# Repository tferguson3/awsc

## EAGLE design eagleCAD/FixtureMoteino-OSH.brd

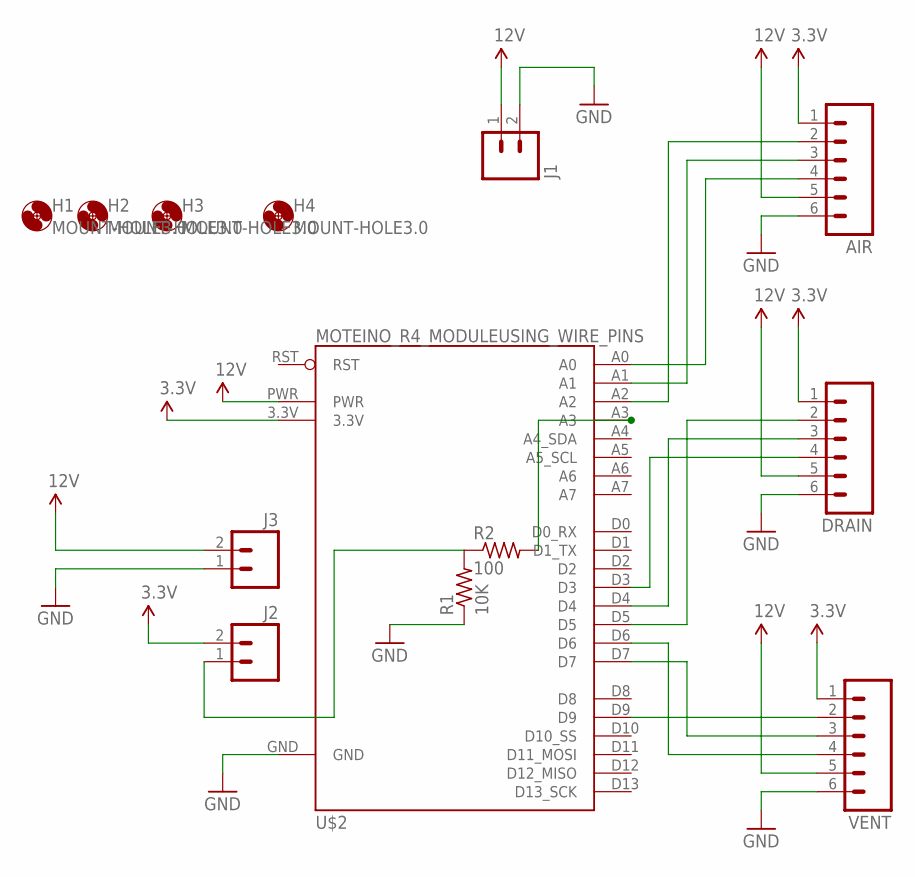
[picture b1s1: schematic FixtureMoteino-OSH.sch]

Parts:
AIR: M06LOCK_LONGPADS; 1X06_LOCK_LONGPADS
DRAIN: M06LOCK_LONGPADS; 1X06_LOCK_LONGPADS
H1, H2, H3, H4: MOUNT-HOLE3.0; 3,0
J1, J2, J3: M025MM; SCREWTERMINAL-5MM-2
R1: 10K; 0207/10
R2: 100; 0207/10
U$2: MOTEINO_R4_MODULEUSING_WIRE_PINS; MOTEINO_R4_WIRE
VENT: M06LOCK_LONGPADS; 1X06_LOCK_LONGPADS

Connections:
3.3V: AIR.1, DRAIN.1, J2.2, U$2.3.3V, VENT.1
12V: AIR.5, DRAIN.5, J1.1, J3.2, U$2.PWR, VENT.5
GND: AIR.6, DRAIN.6, J1.2, J3.1, R1.1, U$2.GND, VENT.6
unnamed: DRAIN.4, U$2.D3
unnamed: DRAIN.3, U$2.D4
unnamed: DRAIN.2, U$2.D5
unnamed: U$2.D6, VENT.4
unnamed: J2.1, R1.2, R2.1
unnamed: U$2.D7, VENT.3
unnamed: U$2.D9, VENT.2
unnamed: AIR.4, U$2.A0
unnamed: AIR.3, U$2.A1
unnamed: AIR.2, U$2.A2
unnamed: R2.2, U$2.A3

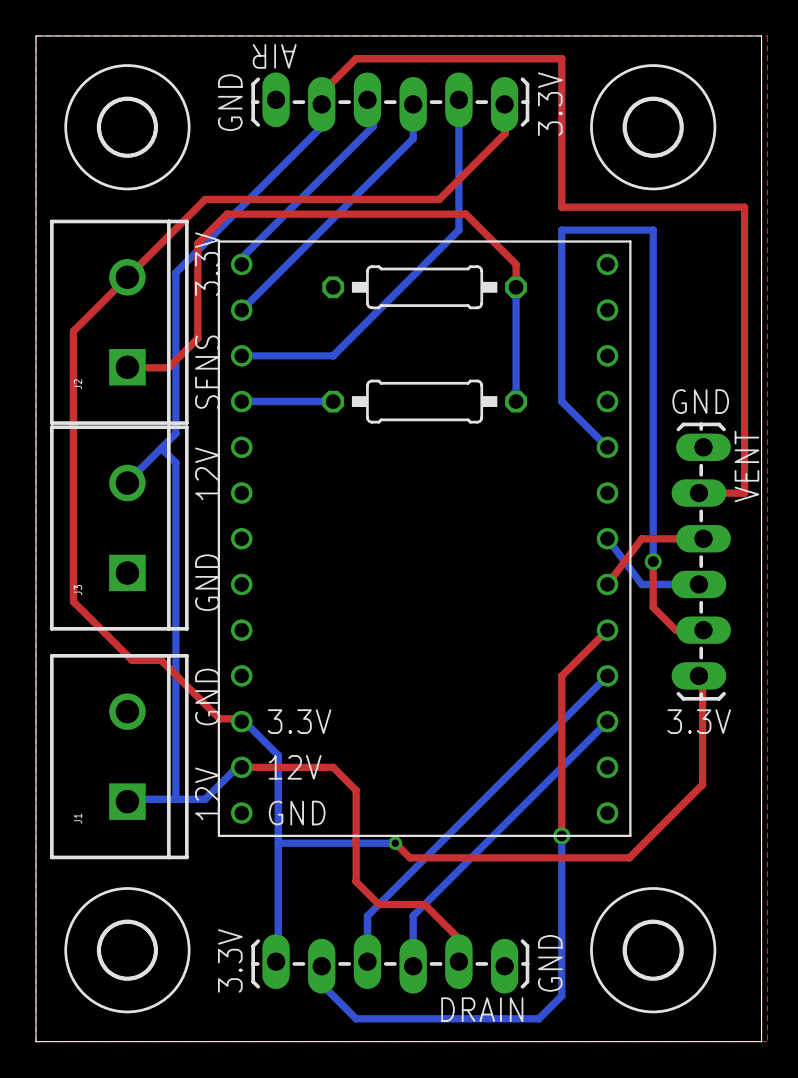
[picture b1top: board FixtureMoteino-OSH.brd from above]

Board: 2 copper layers, 40.3 x 55.9 mm, 14 parts (1 on the bottom side), 14 nets.

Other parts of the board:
U$1: OSHW-LOGO-L

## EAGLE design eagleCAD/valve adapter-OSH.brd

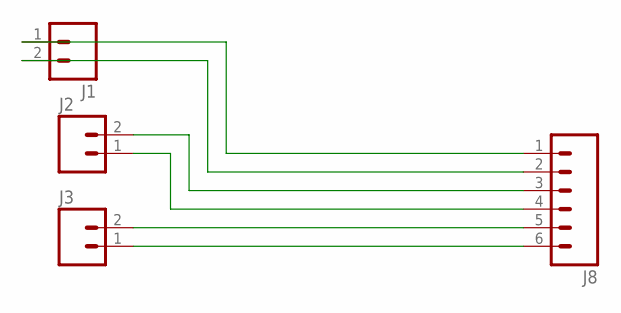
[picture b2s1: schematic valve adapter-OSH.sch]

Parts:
J1, J2, J3: M025MM; SCREWTERMINAL-5MM-2
J8: M06LOCK_LONGPADS; 1X06_LOCK_LONGPADS

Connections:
unnamed: J1.1, J8.1
unnamed: J1.2, J8.2
unnamed: J2.2, J8.3
unnamed: J2.1, J8.4
unnamed: J3.2, J8.5
unnamed: J3.1, J8.6

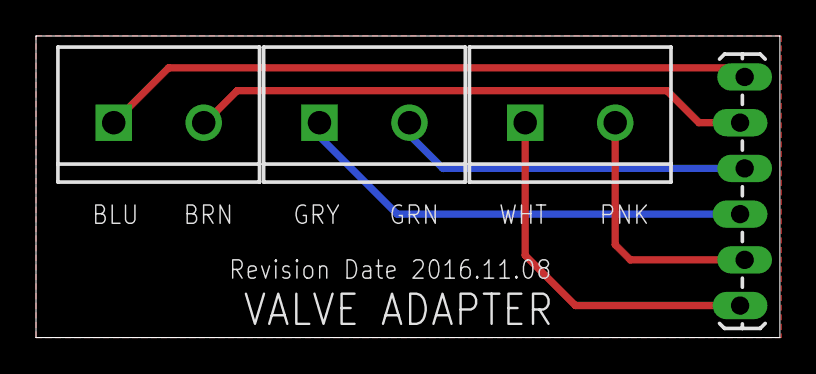
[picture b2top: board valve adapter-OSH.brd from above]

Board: 2 copper layers, 41.3 x 16.8 mm, 5 parts (1 on the bottom side), 6 nets.

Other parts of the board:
U$1: OSHW-LOGO-L

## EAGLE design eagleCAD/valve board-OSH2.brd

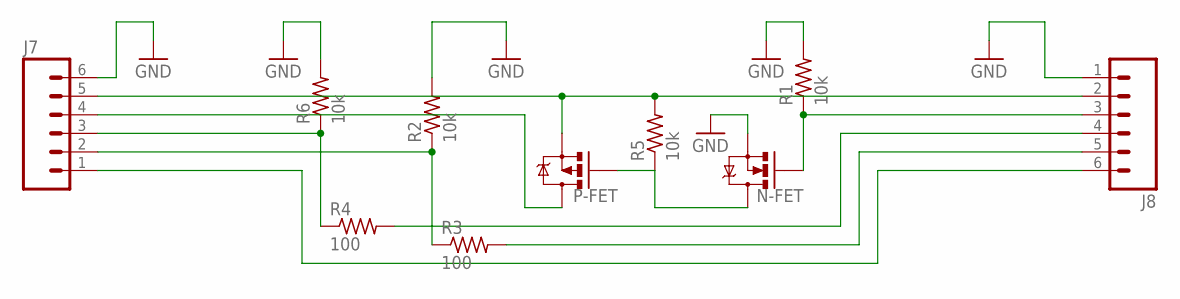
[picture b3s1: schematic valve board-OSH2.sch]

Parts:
J7, J8: M06LOCK_LONGPADS; 1X06_LOCK_LONGPADS
N-FET: MOSFET-NCHANNELFQP30N06L; TO220V
P-FET: MOSFET-PCHANNELFQP27P06; TO220V
R1, R2, R5, R6: 10k; 0207/10
R3, R4: 100; 0207/10

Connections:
GND: J7.6, J8.1, N-FET.3 (S), R1.2, R2.2, R6.2
unnamed: J8.4, R4.2
unnamed: J8.5, R3.2
unnamed: J7.4, P-FET.2 (D)
unnamed: J7.5, J8.2, P-FET.3 (S), R5.2
unnamed: J7.2, R2.1, R3.1
unnamed: N-FET.2 (D), P-FET.1 (G), R5.1
unnamed: J8.3, N-FET.1 (G), R1.1
unnamed: J7.3, R4.1, R6.1
unnamed: J7.1, J8.6

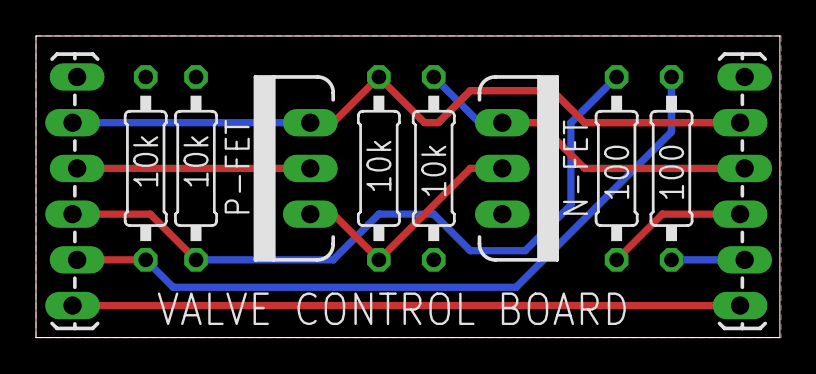
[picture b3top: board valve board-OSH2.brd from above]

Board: 2 copper layers, 41.3 x 16.8 mm, 11 parts (1 on the bottom side), 10 nets.

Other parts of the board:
U$1: OSHW-LOGO-L

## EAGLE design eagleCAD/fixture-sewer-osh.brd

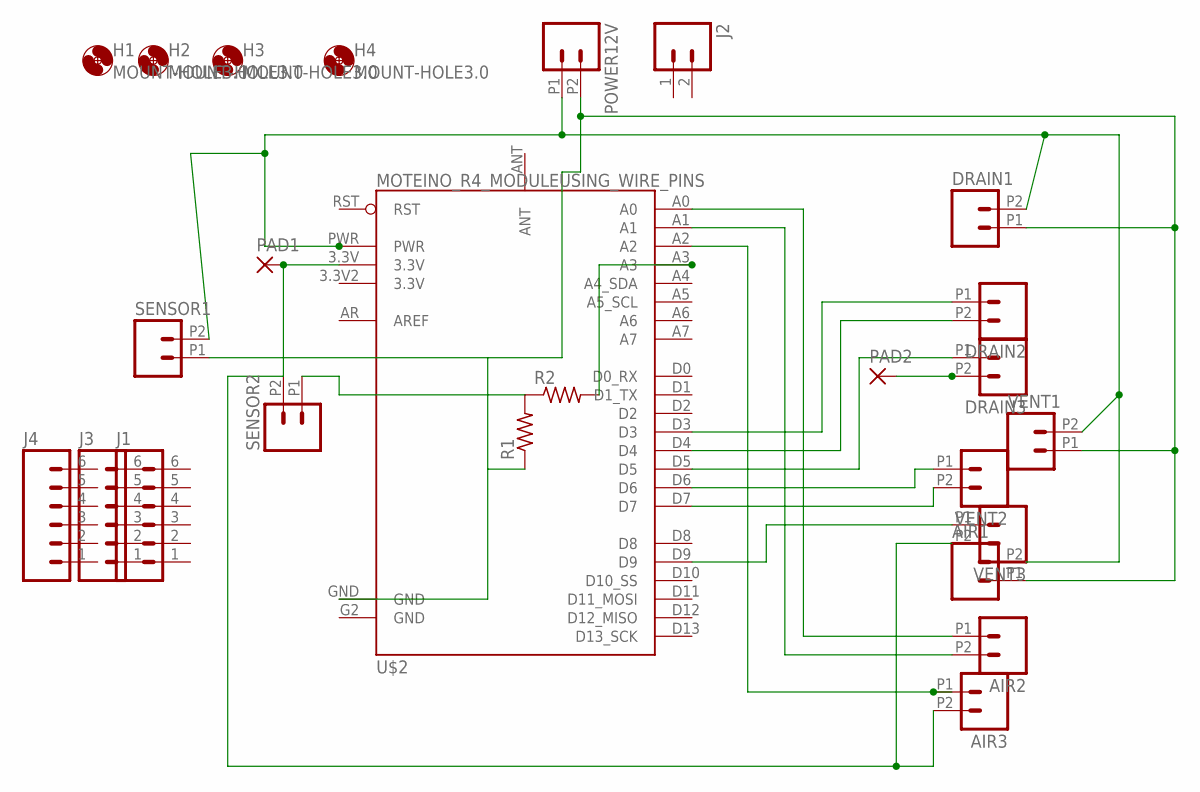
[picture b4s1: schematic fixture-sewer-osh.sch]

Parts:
AIR1, AIR2, AIR3: M022.54MM_SCREWTERM; 1X02_2.54_SCREWTERM
DRAIN1, DRAIN2, DRAIN3: M022.54MM_SCREWTERM; 1X02_2.54_SCREWTERM
H1, H2, H3, H4: MOUNT-HOLE3.0; 3,0
J1, J3, J4: M06LOCK_LONGPADS; 1X06_LOCK_LONGPADS
J2: M025MM; SCREWTERMINAL-5MM-2
PAD1, PAD2: 2,15/1,0
POWER12V: M022.54MM_SCREWTERM; 1X02_2.54_SCREWTERM
R1, R2: R-US_0207/10; 0207/10
SENSOR1, SENSOR2: M022.54MM_SCREWTERM; 1X02_2.54_SCREWTERM
U$2: MOTEINO_R4_MODULEUSING_WIRE_PINS; MOTEINO_R4_WIRE
VENT1, VENT2, VENT3: M022.54MM_SCREWTERM; 1X02_2.54_SCREWTERM

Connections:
GND: AIR1.P1 (1), DRAIN1.P1 (1), POWER12V.P2 (2), R1.1, SENSOR1.P1 (1), U$2.G2 (GND), U$2.GND, VENT1.P1 (1)
unnamed: AIR1.P2 (2), DRAIN1.P2 (2), POWER12V.P1 (1), SENSOR1.P2 (2), U$2.PWR, VENT1.P2 (2)
unnamed: DRAIN2.P1 (1), U$2.D3
unnamed: DRAIN2.P2 (2), U$2.D4
unnamed: DRAIN3.P1 (1), U$2.D5
unnamed: U$2.D6, VENT2.P1 (1)
unnamed: R1.2, R2.1, SENSOR2.P1 (1)
unnamed: U$2.D7, VENT2.P2 (2)
unnamed: U$2.D9, VENT3.P1 (1)
unnamed: AIR2.P1 (1), U$2.A0
unnamed: AIR2.P2 (2), U$2.A1
unnamed: AIR3.P1 (1), U$2.A2
unnamed: DRAIN3.P2 (2), PAD2.1
unnamed: AIR3.P2 (2), PAD1.1, SENSOR2.P2 (2), U$2.3.3V, VENT3.P2 (2)
unnamed: R2.2, U$2.A3

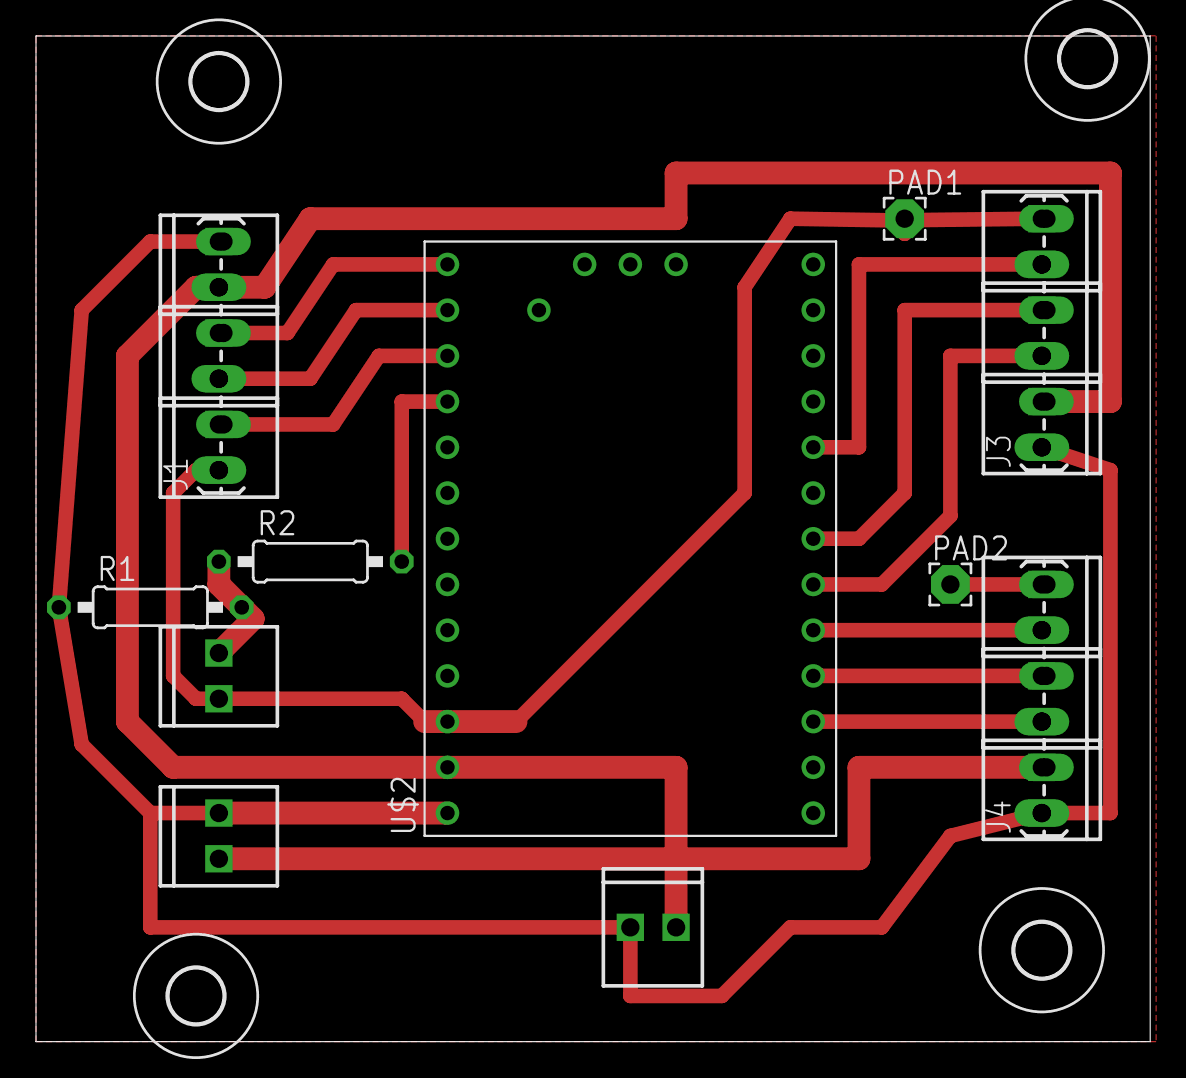
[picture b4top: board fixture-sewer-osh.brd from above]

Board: 2 copper layers, 61.9 x 55.9 mm, 24 parts (0 on the bottom side), 15 nets.

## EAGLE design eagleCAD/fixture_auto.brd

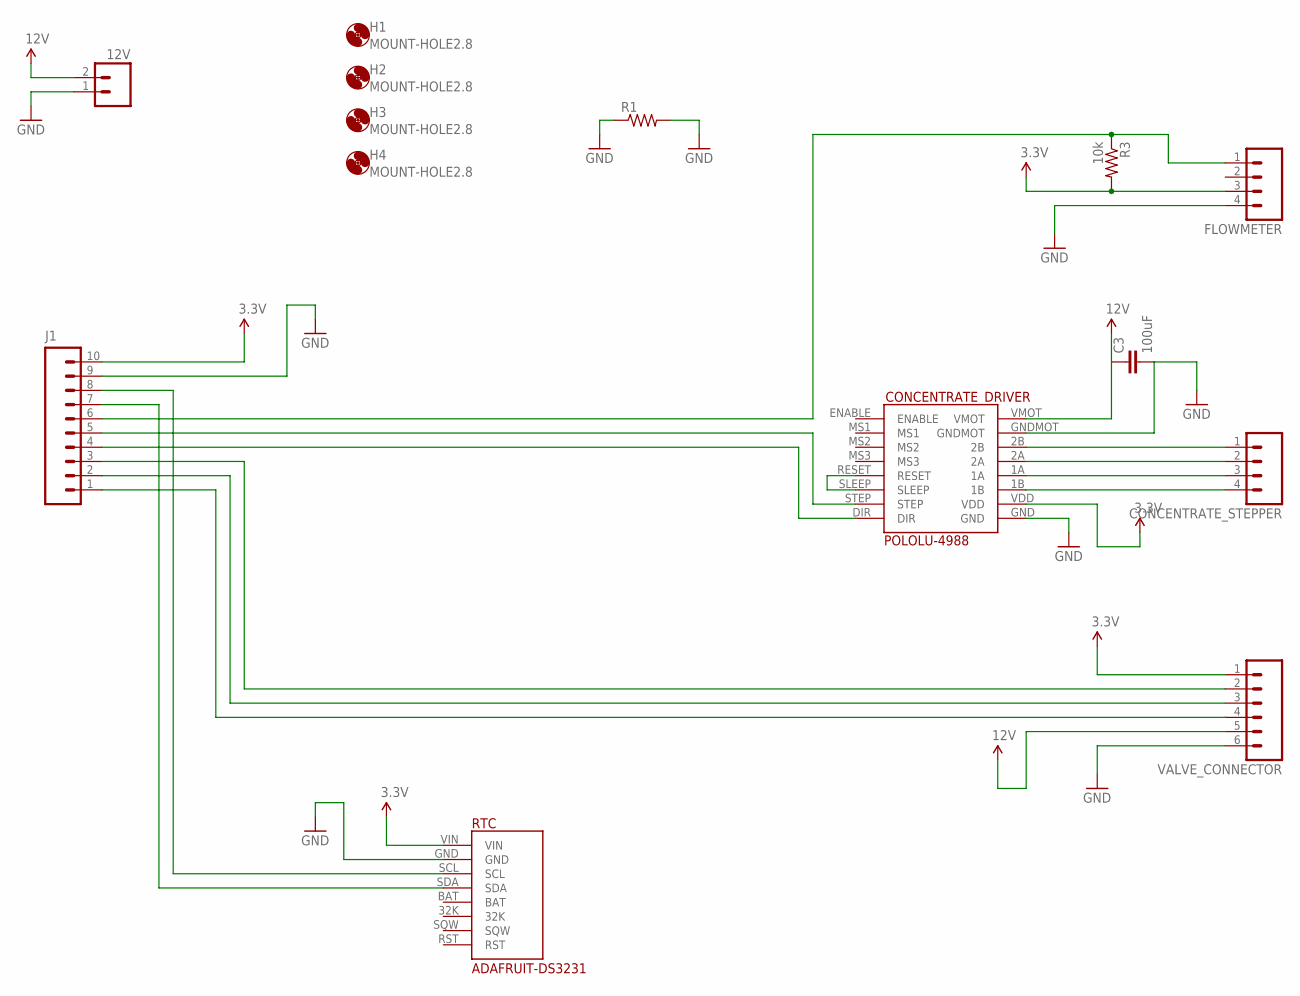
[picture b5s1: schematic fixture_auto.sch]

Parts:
12V: M02LOCK_LONGPADS; 1X02_LOCK_LONGPADS
C3: 100uF; CAP-PTH-SMALL-KIT
CONCENTRATE_DRIVER: POLOLU-4988
CONCENTRATE_STEPPER: M04LOCK_LONGPADS; 1X04_LOCK_LONGPADS
FLOWMETER: M04LOCK_LONGPADS; 1X04_LOCK_LONGPADS
H1, H2, H3, H4: MOUNT-HOLE2.8; 2,8
J1: M10LOCK_LONGPADS; 1X10_LOCK_LONGPADS
R1: RESISTORPTH-1/2W; AXIAL-0.5
R3: 10k; AXIAL-0.3EZ
RTC: ADAFRUIT-DS3231
VALVE_CONNECTOR: M06LOCK_LONGPADS; 1X06_LOCK_LONGPADS

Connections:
3.3V: CONCENTRATE_DRIVER.VDD, FLOWMETER.3, J1.10, R3.P$2 (2), RTC.VIN, VALVE_CONNECTOR.1
12V: 12V.2, C3.1, CONCENTRATE_DRIVER.VMOT, VALVE_CONNECTOR.5
FLOW_PULSE: FLOWMETER.1, J1.6, R3.P$1 (1)
GND: 12V.1, C3.2, CONCENTRATE_DRIVER.GND, CONCENTRATE_DRIVER.GNDMOT, FLOWMETER.4, J1.9, R1.P$1 (1), R1.P$2 (2), RTC.GND, VALVE_CONNECTOR.6
unnamed: J1.3, VALVE_CONNECTOR.2
unnamed: J1.2, VALVE_CONNECTOR.3
unnamed: CONCENTRATE_DRIVER.2B, CONCENTRATE_STEPPER.1
unnamed: J1.1, VALVE_CONNECTOR.4
unnamed: CONCENTRATE_DRIVER.2A, CONCENTRATE_STEPPER.2
unnamed: CONCENTRATE_DRIVER.1A, CONCENTRATE_STEPPER.3
unnamed: CONCENTRATE_DRIVER.1B, CONCENTRATE_STEPPER.4
unnamed: CONCENTRATE_DRIVER.RESET, CONCENTRATE_DRIVER.SLEEP
unnamed: CONCENTRATE_DRIVER.STEP, J1.5
unnamed: CONCENTRATE_DRIVER.DIR, J1.4
unnamed: J1.8, RTC.SCL
unnamed: J1.7, RTC.SDA

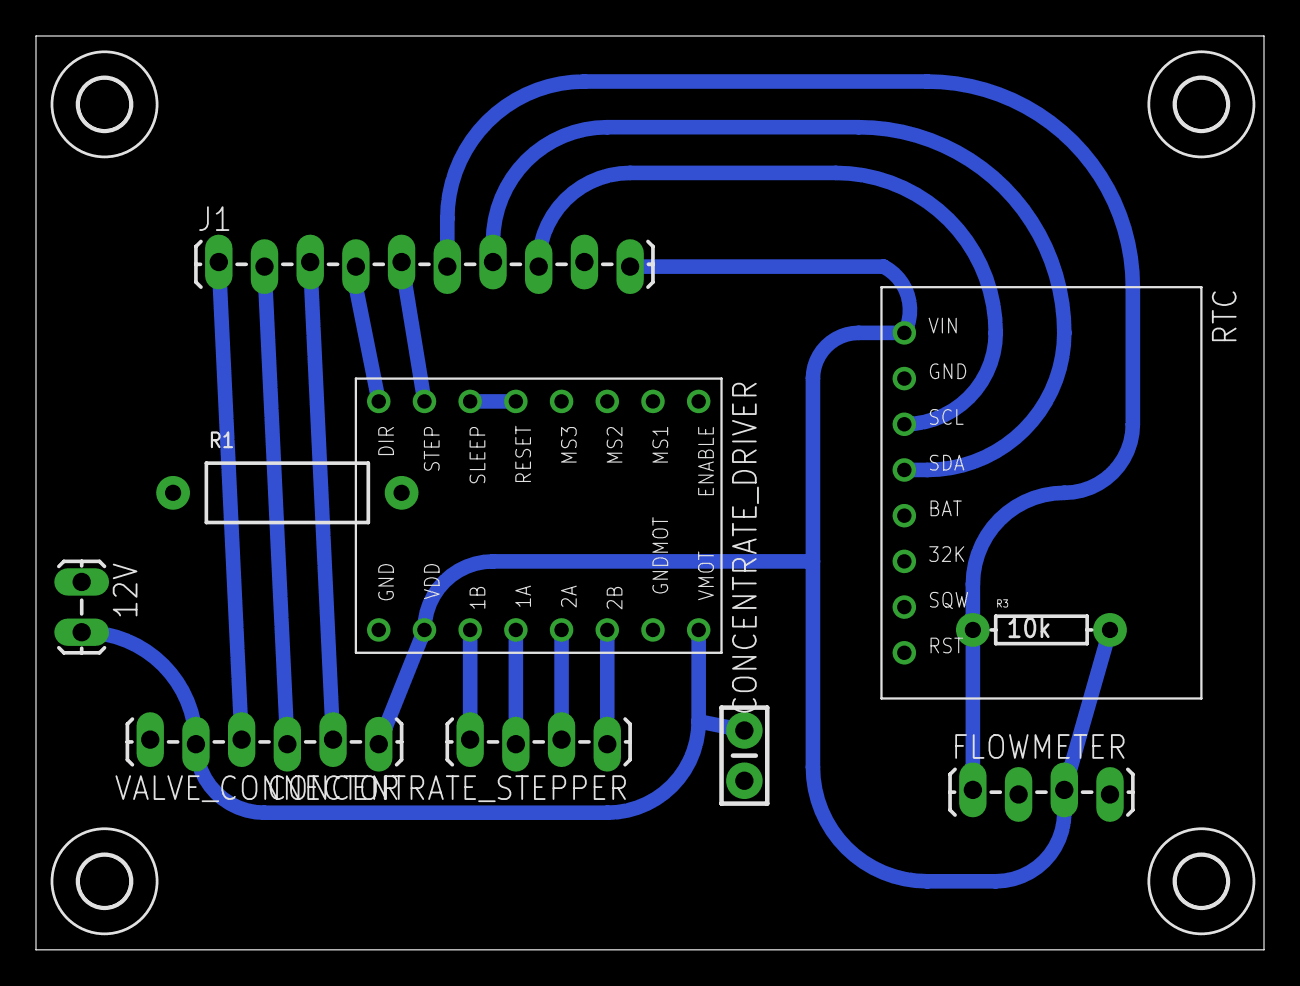
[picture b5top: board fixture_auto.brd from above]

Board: 2 copper layers, 68.2 x 50.8 mm, 14 parts (0 on the bottom side), 16 nets.

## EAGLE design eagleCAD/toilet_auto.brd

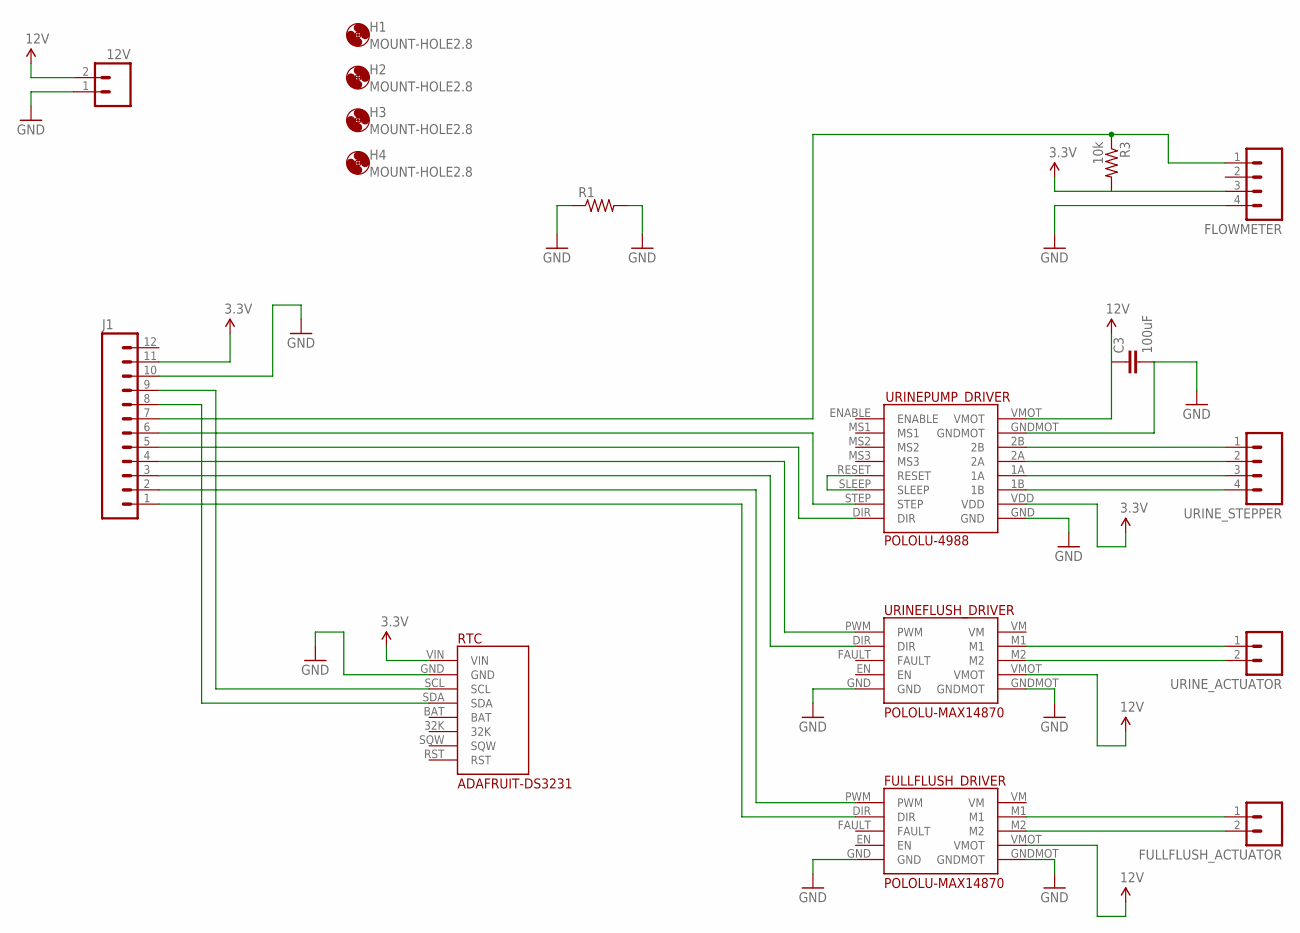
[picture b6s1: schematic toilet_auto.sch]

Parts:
12V: M02LOCK_LONGPADS; 1X02_LOCK_LONGPADS
C3: 100uF; CAP-PTH-SMALL-KIT
FLOWMETER: M04LOCK_LONGPADS; 1X04_LOCK_LONGPADS
FULLFLUSH_ACTUATOR: M02LOCK_LONGPADS; 1X02_LOCK_LONGPADS
FULLFLUSH_DRIVER: POLOLU-MAX14870
H1, H2, H3, H4: MOUNT-HOLE2.8; 2,8
J1: M12LOCK_LONGPADS; 1X12_LOCK_LONGPADS
R1: RESISTORPTH-1/2W; AXIAL-0.5
R3: 10k; AXIAL-0.3EZ
RTC: ADAFRUIT-DS3231
URINEFLUSH_DRIVER: POLOLU-MAX14870
URINEPUMP_DRIVER: POLOLU-4988
URINE_ACTUATOR: M02LOCK_LONGPADS; 1X02_LOCK_LONGPADS
URINE_STEPPER: M04LOCK_LONGPADS; 1X04_LOCK_LONGPADS

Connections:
3.3V: FLOWMETER.3, J1.11, R3.P$2 (2), RTC.VIN, URINEPUMP_DRIVER.VDD
12V: 12V.2, C3.1, FULLFLUSH_DRIVER.VMOT, URINEFLUSH_DRIVER.VMOT, URINEPUMP_DRIVER.VMOT
FLOW_PULSE: FLOWMETER.1, J1.7, R3.P$1 (1)
GND: 12V.1, C3.2, FLOWMETER.4, FULLFLUSH_DRIVER.GND, FULLFLUSH_DRIVER.GNDMOT, J1.10, R1.P$1 (1), R1.P$2 (2), RTC.GND, URINEFLUSH_DRIVER.GND, URINEFLUSH_DRIVER.GNDMOT, URINEPUMP_DRIVER.GND, URINEPUMP_DRIVER.GNDMOT
unnamed: FULLFLUSH_DRIVER.PWM, J1.2
unnamed: URINEFLUSH_DRIVER.M1, URINE_ACTUATOR.1
unnamed: URINEPUMP_DRIVER.2B, URINE_STEPPER.1
unnamed: URINEFLUSH_DRIVER.M2, URINE_ACTUATOR.2
unnamed: FULLFLUSH_ACTUATOR.1, FULLFLUSH_DRIVER.M1
unnamed: FULLFLUSH_ACTUATOR.2, FULLFLUSH_DRIVER.M2
unnamed: URINEPUMP_DRIVER.2A, URINE_STEPPER.2
unnamed: URINEPUMP_DRIVER.1A, URINE_STEPPER.3
unnamed: URINEPUMP_DRIVER.1B, URINE_STEPPER.4
unnamed: URINEPUMP_DRIVER.RESET, URINEPUMP_DRIVER.SLEEP
unnamed: J1.5, URINEPUMP_DRIVER.DIR
unnamed: J1.6, URINEPUMP_DRIVER.STEP
unnamed: J1.4, URINEFLUSH_DRIVER.PWM
unnamed: J1.3, URINEFLUSH_DRIVER.DIR
unnamed: FULLFLUSH_DRIVER.DIR, J1.1
unnamed: J1.9, RTC.SCL
unnamed: J1.8, RTC.SDA

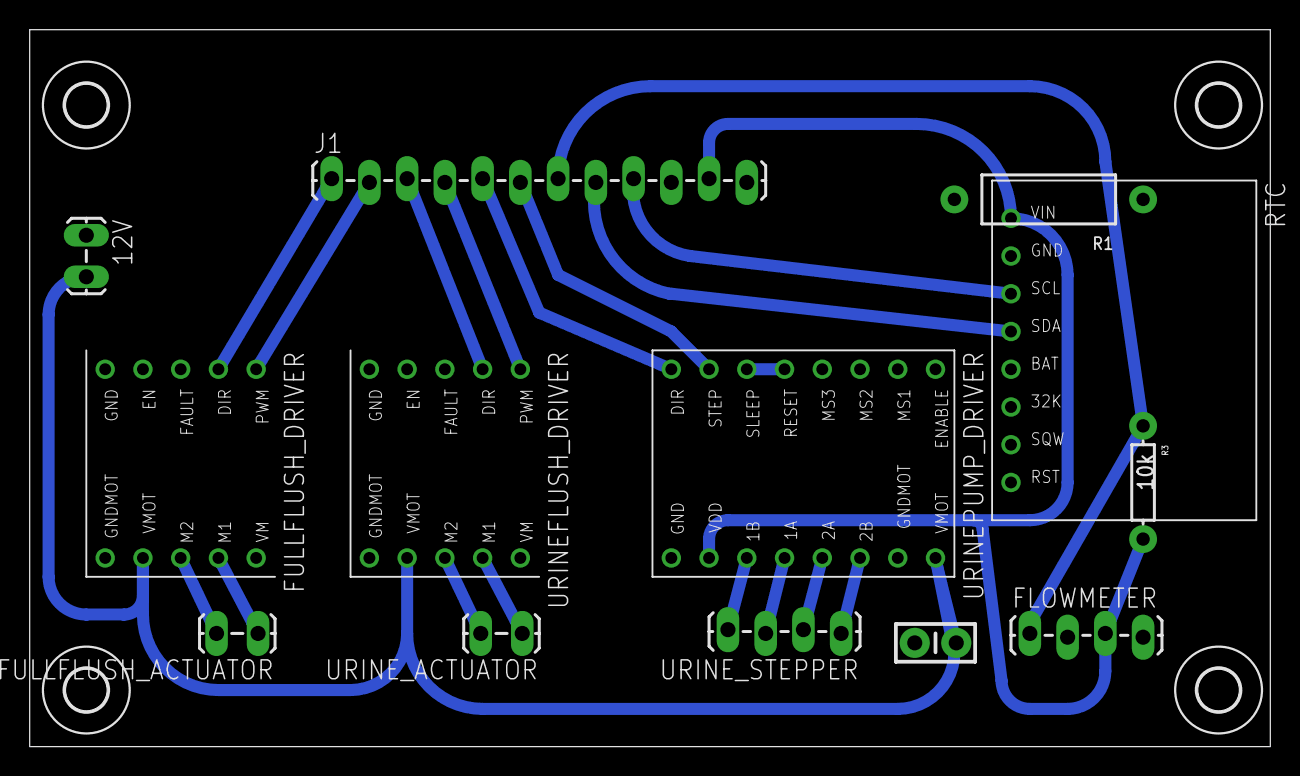
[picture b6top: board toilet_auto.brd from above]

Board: 2 copper layers, 83.5 x 48.2 mm, 17 parts (0 on the bottom side), 21 nets.

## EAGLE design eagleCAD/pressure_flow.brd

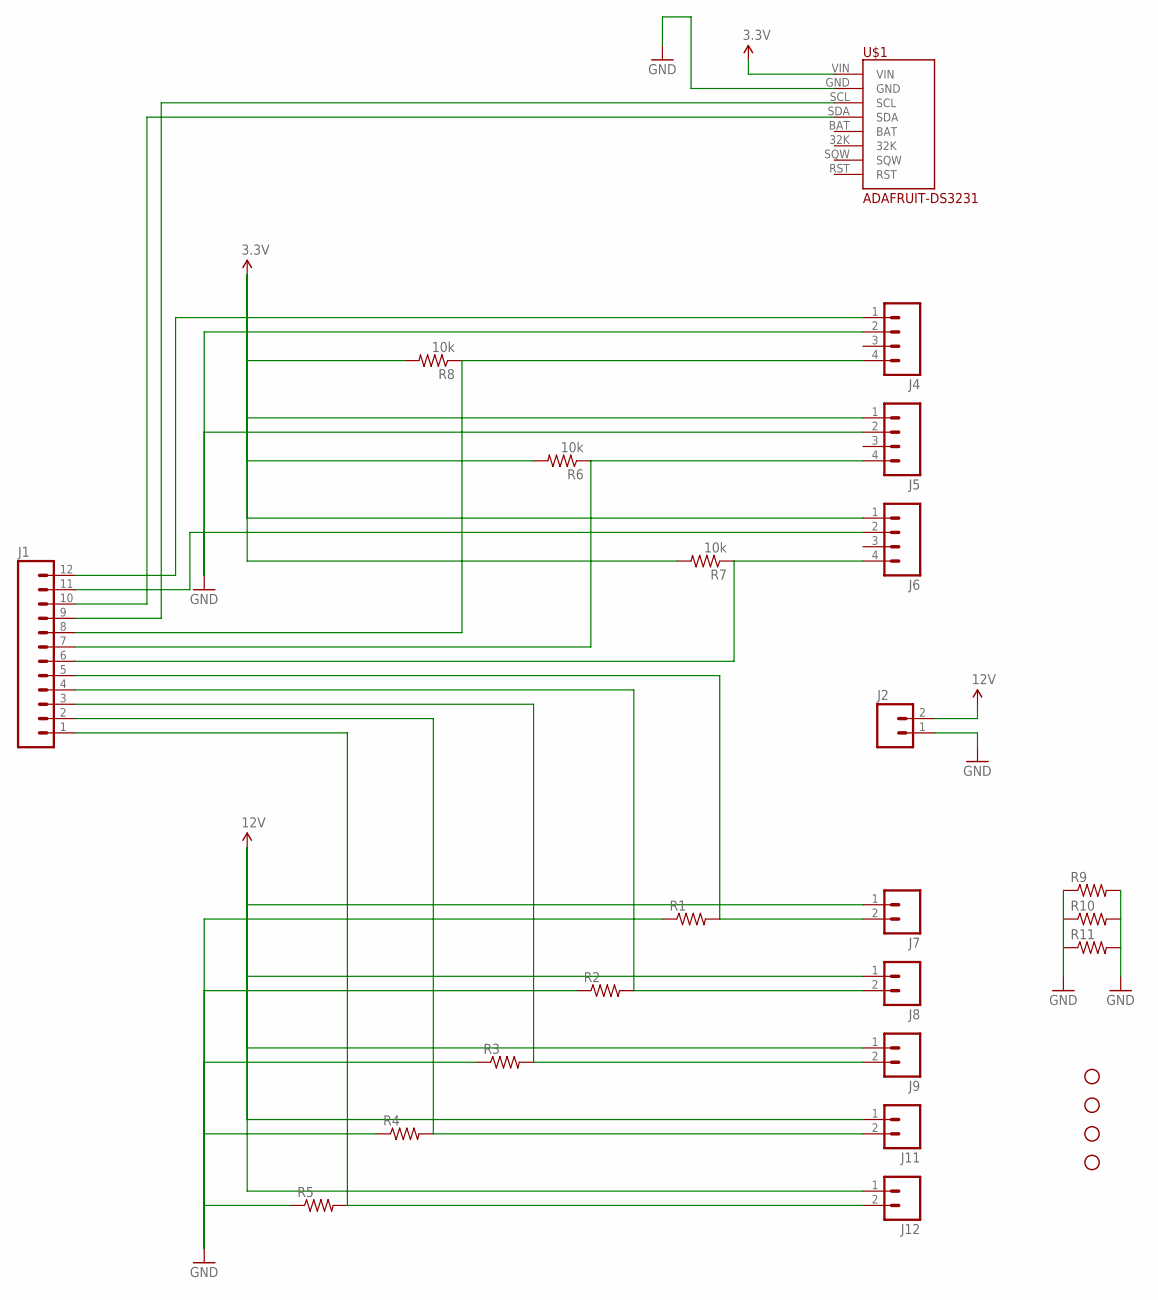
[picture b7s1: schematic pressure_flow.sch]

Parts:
H1, H2, H3, H4: STAND-OFF
J1: M12LOCK_LONGPADS; 1X12_LOCK_LONGPADS
J2, J7, J8, J9, J11, J12: M02LOCK_LONGPADS; 1X02_LOCK_LONGPADS
J4, J5, J6: M04LOCK_LONGPADS; 1X04_LOCK_LONGPADS
R1, R2, R3, R4, R5, R9, R10, R11: RESISTORPTH-1/2W; AXIAL-0.5
R6, R7, R8: 10k; AXIAL-0.3
U$1: ADAFRUIT-DS3231

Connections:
3.3V: J1.12, J4.1, J5.1, J6.1, R6.P$2 (2), R7.P$2 (2), R8.P$2 (2), U$1.VIN
12V: J2.2, J7.1, J8.1, J9.1, J11.1, J12.1
GND: J1.11, J2.1, J4.2, J5.2, J6.2, R1.P$1 (1), R2.P$1 (1), R3.P$1 (1), R4.P$1 (1), R5.P$1 (1), R9.P$1 (1), R9.P$2 (2), R10.P$1 (1), R10.P$2 (2), R11.P$1 (1), R11.P$2 (2), U$1.GND
unnamed: J1.5, J7.2, R1.P$2 (2)
unnamed: J1.4, J8.2, R2.P$2 (2)
unnamed: J1.2, J11.2, R4.P$2 (2)
unnamed: J1.1, J12.2, R5.P$2 (2)
unnamed: J1.9, U$1.SCL
unnamed: J1.6, J6.4, R7.P$1 (1)
unnamed: J1.8, J4.4, R8.P$1 (1)
unnamed: J1.7, J5.4, R6.P$1 (1)
unnamed: J1.10, U$1.SDA
unnamed: J1.3, J9.2, R3.P$2 (2)

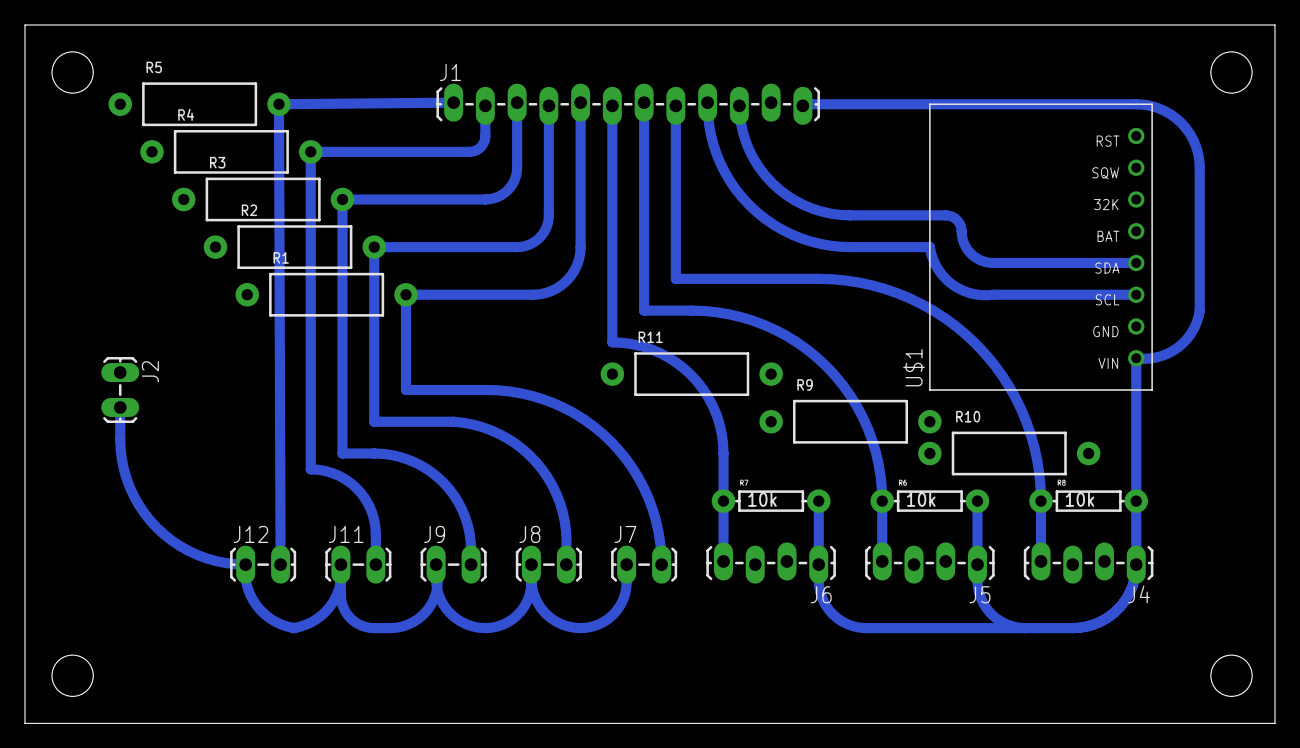
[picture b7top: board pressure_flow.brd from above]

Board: 2 copper layers, 100.0 x 55.9 mm, 26 parts (0 on the bottom side), 13 nets.

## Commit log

2016-07-06 added directory
2016-07-06 added eagle files in directory
2016-07-06 updated toilet schematic
2016-07-06 added fixture auto schematic
2016-07-06 added power monitoring schematic
2016-07-06 added ds_store to gitignore
2016-07-06 removed ds_store
2016-07-06 added WOW to licence
2016-07-06 Removed WOW
2016-07-07 updated power monitor with clock
2016-07-07 ground plane and spacing
2016-07-07 updated fixture schematic
2016-07-07 added flow pressure board and schematic
2016-07-08 revised fixture board
2016-07-08 revised toilet board
2016-07-08 finalize for mill
2016-07-09 adapted fixture board for OSHpark print
2016-07-09 minor corrections
2016-07-09 added stepper test code
2016-07-09 updates and 1st draft of toilet OSH
2016-07-10 minor trace routing update
2016-07-10 updates labeling
2016-07-11 boards uploaded to github
2016-07-11 updated to that on bob
2016-07-11 added valve test
2016-07-12 revise valve board for oshpark
2016-07-12 replaced missing code
2016-07-13 added more test code
2016-07-13 added water heater code
2016-07-13 added hacked together flowmeter test sketch
2016-07-15 added modified power monitoring program
2016-07-16 minor revisions (must correct fixtures)
2016-07-17 minor revisions
    must load jumper settings and number of fixtures when uploaded
2016-07-17 update added date stamp and identifed 2 file names
2016-07-17 minor changes
2016-07-17 added comment on subsequent day header missing
2016-07-19 added flow frequency code
2016-07-19 updated pressure monitoring
2016-07-19 revised with max flow restriction
2016-07-19 correct pasted wrap issues
2016-07-20 set minimum frequency at 50 hz
2016-07-20 added variables for pins
2016-07-20 updated flowfreq with logging
2016-07-20 debugged flowfreq.py with logging
2016-07-20 more debugging seems to work, not tested with flow
2016-11-04 adding flux analysis program
2016-11-07 updated pcb valve
2016-11-08 added new fixture board
2016-11-08 updated valve board osh2
2016-11-08 added adapter board
2016-11-09 updaed moteino fixture board
2016-11-10 updated fixture board
2016-11-10 added valve board left
2016-11-11 updated boards
2016-11-14 minor update
2016-11-14 updates ready for osh
2016-11-17 test
2016-11-17 testing pull/push
2016-12-05 testflux edit to avoid noise
2017-03-29 new flux code for tab WWT
2017-03-29 added cut off sections
2017-03-29 fis file noame
2017-03-29 updates from errors
2017-03-29 should be ready to test
2017-07-03 AWSCpumptiming
2017-08-24 created for flat sheet membrane tests
2017-08-28 tab separated values no labels
2017-08-31 drop size correcction
2017-11-29 cleaned code
2017-12-13 sbr preliminary code
2017-12-15 one stepper and 5 on off functinos
2017-12-16 filtration
2017-12-16 gac start
2017-12-18 sequence added 4 test
2017-12-18 no presssure carryover and 15sec interval
2017-12-28 test run
2017-12-28 log arduino serial for GAC
2017-12-29 added days of week for scheduling
2017-12-29 setup for desktop
2017-12-29 Rename ardLogGAC.py to GAC/ardLogGAC.py
2017-12-29 Rename ardLogFilter.py to filtration/ardLogFilter.py
2017-12-29 add pump shutoff at 8hr
2018-01-03 corrected equation
2018-01-04 added ras loading function and stir insome other places
2018-01-05 fillup and set up weekend cycle
2018-01-09 new fill and cycle sequence
2018-01-25 change to run over weekend and fill to only 21gal
2018-01-29 addd flag to fix shutoff at 75psi
2018-01-29 add pump shutoff @ 20psi
2018-01-31 start 1hr later
2018-02-01 change rest to no aeration and change normal sequence slightly
2018-02-05 changed start time to later and 2 more hrs of air
2018-02-06 change airation cycle again
    air 30 sec 2 hrs
    air 1 min on 3 off 1 hr
    5 on 5 off 1 hr
    all on 1 hr
2018-02-15 start hour early and complete air cycle corretion
2018-03-27 Create granular_sludge
2018-03-28 Update granular_sludge
2018-04-09 waste half of previous automatic withdrawl
2018-04-13 sec display and test code
2018-04-17 30 sec air and timing fix
2018-09-06 commented and deleted old useless stuff
2018-09-06 extra space
2018-09-06 TFF Comments
2018-09-07 TFFEdits
    Changed timing to Friday to test code
2018-09-07 Changed timing on sequence

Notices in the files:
parts and their libraries:
SparkFun-Connectors: Licensing: Creative Commons ShareAlike 4.0 International - https://creativecommons.org/licenses/by-sa/4.0
